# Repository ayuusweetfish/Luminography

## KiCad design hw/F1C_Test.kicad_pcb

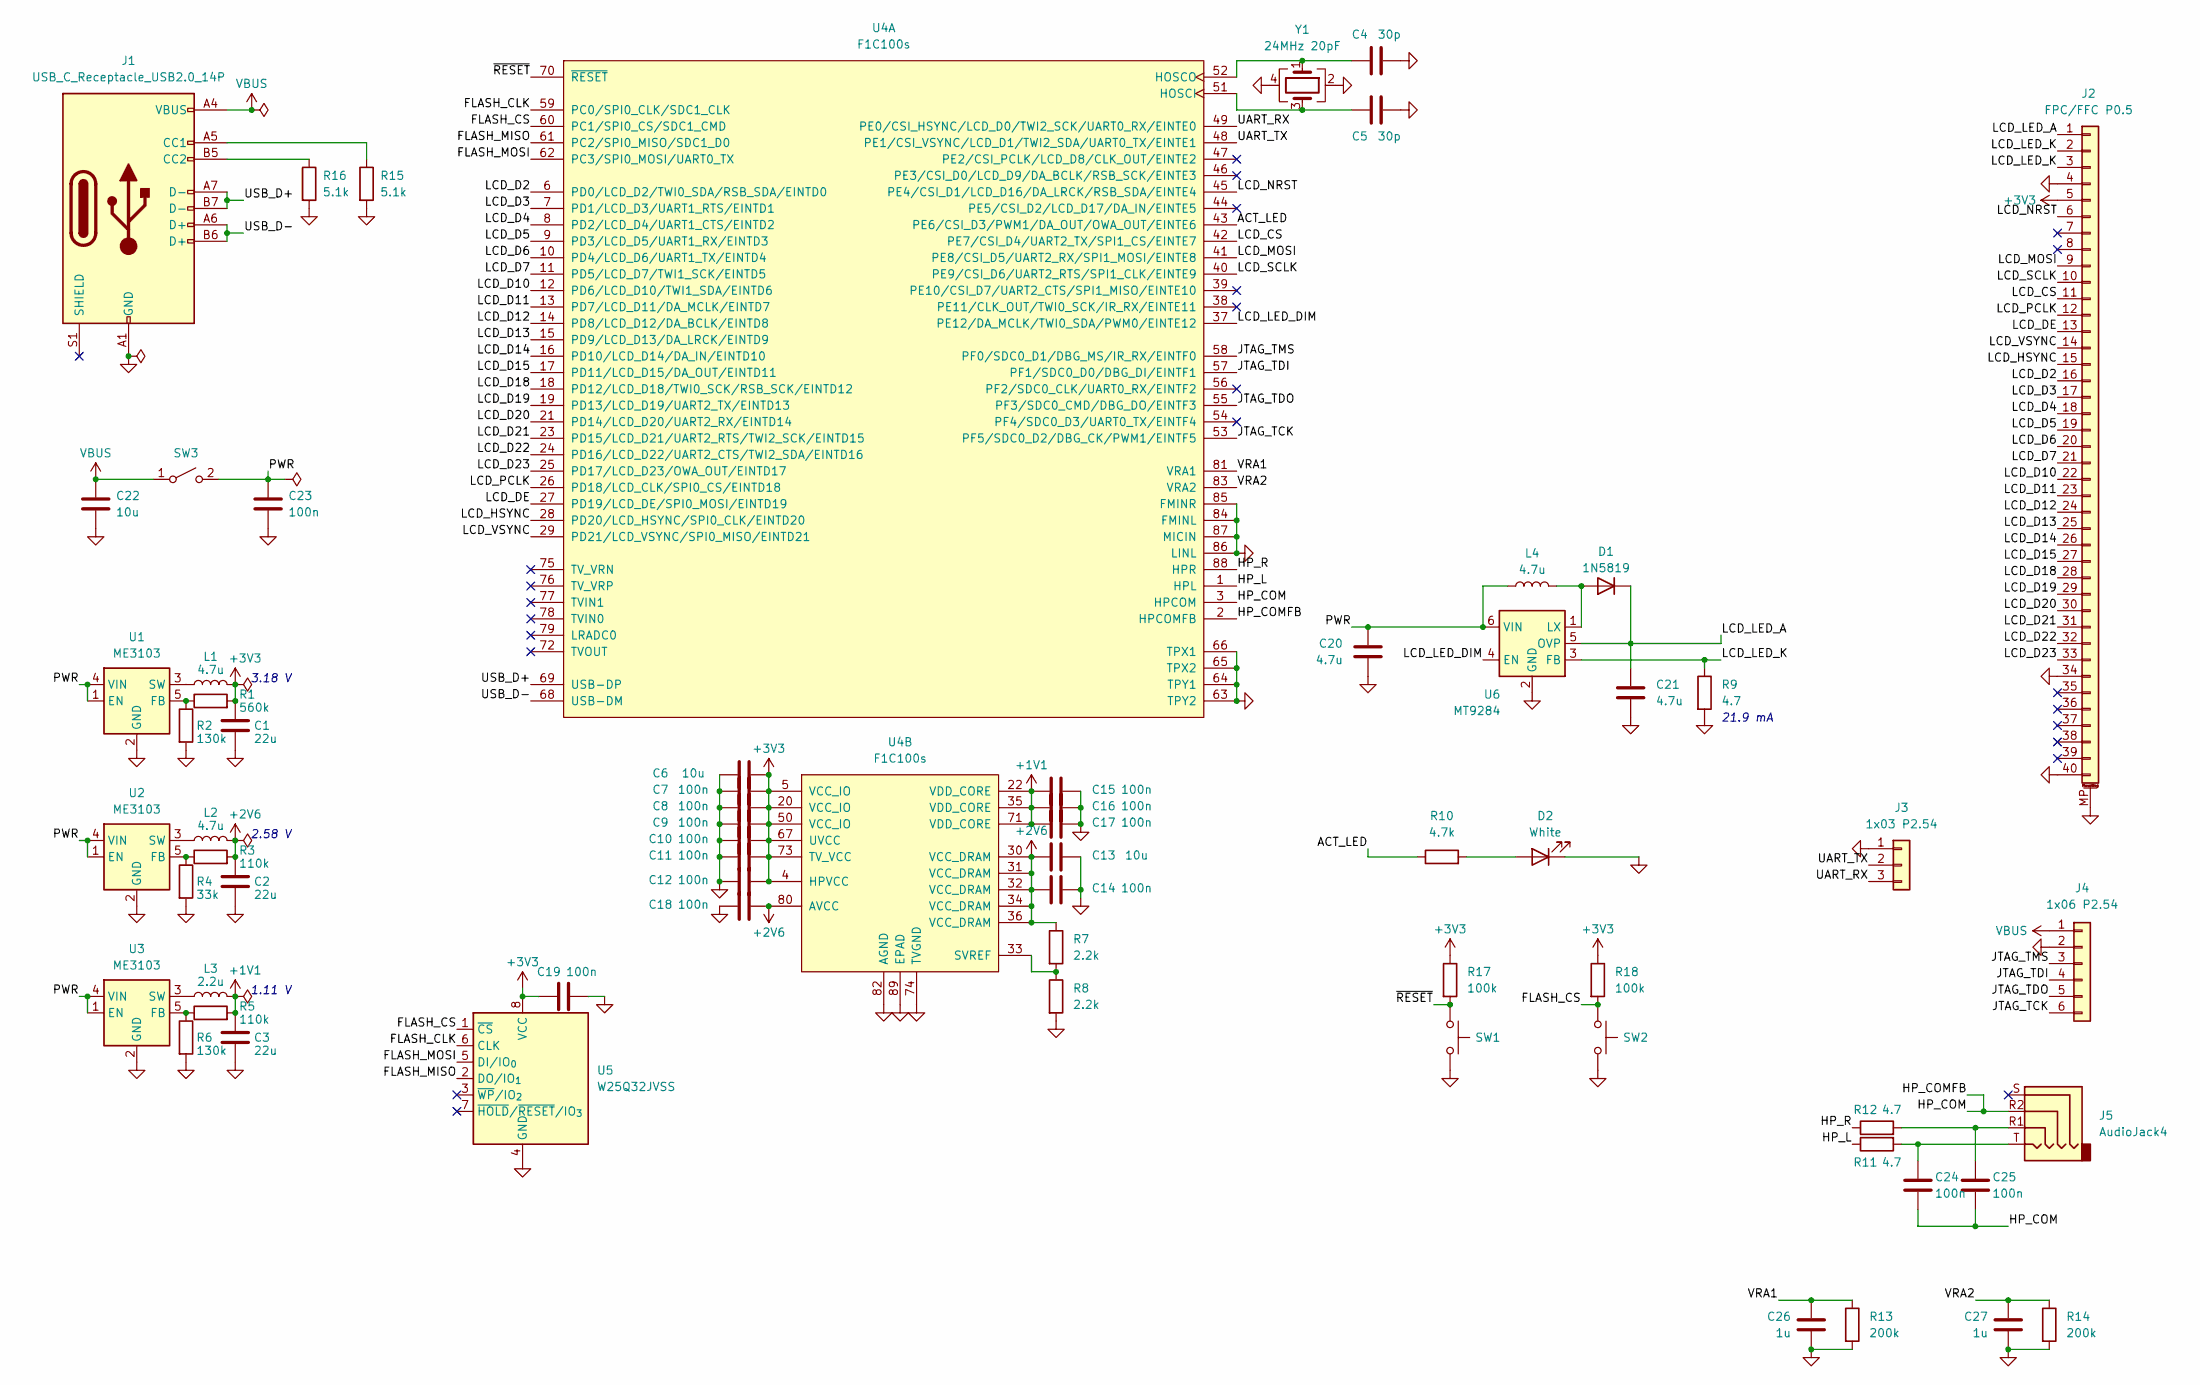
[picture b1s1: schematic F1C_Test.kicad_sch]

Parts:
C1, C2, C3: 22u; C_0603_1608Metric
C4, C5: 30p; C_0402_1005Metric
C6, C13, C22: 10u; C_0402_1005Metric
C7, C8, C9, C10, C11, C12, C14, C15, C16, C17, C18, C19, C23, C24, C25: 100n; C_0402_1005Metric
C20, C21: 4.7u; C_0402_1005Metric
C26, C27: 1u; C_0402_1005Metric
D1: 1N5819; D_SOD-323
D2: White; LED_0603_1608Metric
J1: USB_C_Receptacle_USB2.0_14P; USB_C_Receptacle_HRO_TYPE-C-31-M-12; LCSC PN C165948
J2: FPC/FFC P0.5; FPC_1x40_P0.5_R
J3: 1x03 P2.54; PinHeader_1x03_P2.54mm_Vertical
J4: 1x06 P2.54; PinHeader_1x06_P2.54mm_Vertical
J5: AudioJack4; Jack_3.5mm_KoreanHropartsElec_PJ-320D-4A_Horizontal
L1, L2, L4: 4.7u; L_Sunlord_SWPA3015S
L3: 2.2u; L_Sunlord_SWPA3015S
R1: 560k; R_0402_1005Metric
R2, R6: 130k; R_0402_1005Metric
R3, R5: 110k; R_0402_1005Metric
R4: 33k; R_0402_1005Metric
R7, R8: 2.2k; R_0402_1005Metric
R9, R11, R12: 4.7; R_0402_1005Metric
R10: 4.7k; R_0402_1005Metric
R13, R14: 200k; R_0402_1005Metric
R15, R16: 5.1k; R_0402_1005Metric
R17, R18: 100k; R_0402_1005Metric
SW1, SW2: SW_Push; SW_Push_1TS009xxxx-xxxx-xxxx_6x6x5mm
SW3: SW_SPST; SPST_1x01_P2.54
U1, U2, U3: ME3103; SOT-23-5
U4: F1C100s; QFN40P1000X1000X90-89N-D
U5: W25Q32JVSS; SOIC-8_5.3x5.3mm_P1.27mm
U6: MT9284; SOT-23-6
Y1: 24MHz 20pF; Crystal_SMD_3225-4Pin_3.2x2.5mm; LCSC PN C5339095

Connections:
+1V1: C3.1, C15.2, C16.2, C17.2, L3.2, R5.2, U4.22 (VDD_CORE), U4.35 (VDD_CORE), U4.71 (VDD_CORE)
+2V6: C2.1, C13.2, C14.2, C18.2, L2.2, R3.2, R7.1, U4.30 (VCC_DRAM), U4.31 (VCC_DRAM), U4.32 (VCC_DRAM), U4.34 (VCC_DRAM), U4.36 (VCC_DRAM), U4.80 (AVCC)
+3V3: C1.1, C6.2, C7.2, C8.2, C9.2, C10.2, C11.2, C12.2, C19.1, J2.5, L1.2, R1.2, R17.1, R18.1, U4.4 (HPVCC), U4.5 (VCC_IO), U4.20 (VCC_IO), U4.50 (VCC_IO), U4.67 (UVCC), U4.73 (TV_VCC), U5.8 (VCC)
/ACT_LED: R10.1, U4.43 (PE6/CSI_D3/PWM1/DA_OUT/OWA_OUT/EINTE6)
/FLASH_CLK: U4.59 (PC0/SPI0_CLK/SDC1_CLK), U5.6 (CLK)
/FLASH_CS: R18.2, SW2.1, U4.60 (PC1/SPI0_CS/SDC1_CMD), U5.1 (~CS)
/FLASH_MISO: U4.61 (PC2/SPI0_MISO/SDC1_D0), U5.2 (DO/IO_{1})
/FLASH_MOSI: U4.62 (PC3/SPI0_MOSI/UART0_TX), U5.5 (DI/IO_{0})
/HP_COM: C24.2, C25.2, J5.R2, U4.2 (HPCOMFB), U4.3 (HPCOM)
/HP_L: R11.1, U4.1 (HPL)
/HP_R: R12.1, U4.88 (HPR)
/JTAG_TCK: J4.6, U4.53 (PF5/SDC0_D2/DBG_CK/PWM1/EINTF5)
/JTAG_TDI: J4.4, U4.57 (PF1/SDC0_D0/DBG_DI/EINTF1)
/JTAG_TDO: J4.5, U4.55 (PF3/SDC0_CMD/DBG_DO/EINTF3)
/JTAG_TMS: J4.3, U4.58 (PF0/SDC0_D1/DBG_MS/IR_RX/EINTF0)
/LCD_CS: J2.11, U4.42 (PE7/CSI_D4/UART2_TX/SPI1_CS/EINTE7)
/LCD_D2: J2.16, U4.6 (PD0/LCD_D2/TWI0_SDA/RSB_SDA/EINTD0)
/LCD_D3: J2.17, U4.7 (PD1/LCD_D3/UART1_RTS/EINTD1)
/LCD_D4: J2.18, U4.8 (PD2/LCD_D4/UART1_CTS/EINTD2)
/LCD_D5: J2.19, U4.9 (PD3/LCD_D5/UART1_RX/EINTD3)
/LCD_D6: J2.20, U4.10 (PD4/LCD_D6/UART1_TX/EINTD4)
/LCD_D7: J2.21, U4.11 (PD5/LCD_D7/TWI1_SCK/EINTD5)
/LCD_D10: J2.22, U4.12 (PD6/LCD_D10/TWI1_SDA/EINTD6)
/LCD_D11: J2.23, U4.13 (PD7/LCD_D11/DA_MCLK/EINTD7)
/LCD_D12: J2.24, U4.14 (PD8/LCD_D12/DA_BCLK/EINTD8)
/LCD_D13: J2.25, U4.15 (PD9/LCD_D13/DA_LRCK/EINTD9)
/LCD_D14: J2.26, U4.16 (PD10/LCD_D14/DA_IN/EINTD10)
/LCD_D15: J2.27, U4.17 (PD11/LCD_D15/DA_OUT/EINTD11)
/LCD_D18: J2.28, U4.18 (PD12/LCD_D18/TWI0_SCK/RSB_SCK/EINTD12)
/LCD_D19: J2.29, U4.19 (PD13/LCD_D19/UART2_TX/EINTD13)
/LCD_D20: J2.30, U4.21 (PD14/LCD_D20/UART2_RX/EINTD14)
/LCD_D21: J2.31, U4.23 (PD15/LCD_D21/UART2_RTS/TWI2_SCK/EINTD15)
/LCD_D22: J2.32, U4.24 (PD16/LCD_D22/UART2_CTS/TWI2_SDA/EINTD16)
/LCD_D23: J2.33, U4.25 (PD17/LCD_D23/OWA_OUT/EINTD17)
/LCD_DE: J2.13, U4.27 (PD19/LCD_DE/SPI0_MOSI/EINTD19)
/LCD_HSYNC: J2.15, U4.28 (PD20/LCD_HSYNC/SPI0_CLK/EINTD20)
/LCD_LED_A: C21.1, D1.1 (K), J2.1, U6.5 (OVP)
/LCD_LED_DIM: U4.37 (PE12/DA_MCLK/TWI0_SDA/PWM0/EINTE12), U6.4 (EN)
/LCD_LED_K: J2.2, J2.3, R9.1, U6.3 (FB)
/LCD_MOSI: J2.9, U4.41 (PE8/CSI_D5/UART2_RX/SPI1_MOSI/EINTE8)
/LCD_NRST: J2.6, U4.45 (PE4/CSI_D1/LCD_D16/DA_LRCK/RSB_SDA/EINT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)
/LCD_PCLK: J2.12, U4.26 (PD18/LCD_CLK/SPI0_CS/EINTD18)
/LCD_SCLK: J2.10, U4.40 (PE9/CSI_D6/UART2_RTS/SPI1_CLK/EINTE9)
/LCD_VSYNC: J2.14, U4.29 (PD21/LCD_VSYNC/SPI0_MISO/EINTD21)
/PWR: C20.1, C23.1, L4.1, SW3.2 (B), U1.1 (EN), U1.4 (VIN), U2.1 (EN), U2.4 (VIN), U3.1 (EN), U3.4 (VIN), U6.6 (VIN)
/UART_RX: J3.3, U4.49 (PE0/CSI_HSYNC/LCD_D0/TWI2_SCK/UART0_RX/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)
/UART_TX: J3.2, U4.48 (PE1/CSI_VSYNC/LCD_D1/TWI2_SDA/UART0_TX/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)
/USB_D+: J1.A7 (D-), J1.B7 (D-), U4.69 (USB-DP)
/USB_D-: J1.A6 (D+), J1.B6 (D+), U4.68 (USB-DM)
/VRA1: C26.1, R13.1, U4.81 (VRA1)
/VRA2: C27.1, R14.1, U4.83 (VRA2)
/~RESET: R17.2, SW1.1, U4.70 (~RESET)
GND: C1.2, C2.2, C3.2, C4.2, C5.2, C6.1, C7.1, C8.1, C9.1, C10.1, C11.1, C12.1, C13.1, C14.1, C15.1, C16.1, C17.1, C18.1, C19.2, C20.2, C21.2, C22.2, C23.2, C26.2, C27.2, D2.1 (K), J1.A1 (GND), J1.A12 (GND), J1.B1 (GND), J1.B12 (GND), J2.4, J2.34, J2.40, J2.MP (MountPin), J3.1, J4.2, R2.2, R4.2, R6.2, R8.2, R9.2, R13.2, R14.2, R15.2, R16.2, SW1.2, SW2.2, U1.2 (GND), U2.2 (GND), U3.2 (GND), U4.63 (TPY2), U4.64 (TPY1), U4.65 (TPX2), U4.66 (TPX1), U4.74 (TVGND), U4.82 (AGND), U4.84 (FMINL), U4.85 (FMINR), U4.86 (LINL), U4.87 (MICIN), U4.89 (EPAD), U5.4 (GND), U6.2 (GND), Y1.2, Y1.4
unnamed: C24.1, J5.T, R11.2
unnamed: C25.1, J5.R1, R12.2
unnamed: D1.2 (A), L4.2, U6.1 (LX)
unnamed: D2.2 (A), R10.2
unnamed: J1.A5 (CC1), R15.1
unnamed: J1.B5 (CC2), R16.1
unnamed: R1.1, R2.1, U1.5 (FB)
unnamed: L1.1, U1.3 (SW)
unnamed: R3.1, R4.1, U2.5 (FB)
unnamed: L2.1, U2.3 (SW)
unnamed: R5.1, R6.1, U3.5 (FB)
unnamed: L3.1, U3.3 (SW)
unnamed: C5.1, U4.51 (HOSCI), Y1.3
unnamed: C4.1, U4.52 (HOSCO), Y1.1
unnamed: R7.2, R8.1, U4.33 (SVREF)
VBUS: C22.1, J1.A4 (VBUS), J1.A9 (VBUS), J1.B4 (VBUS), J1.B9 (VBUS), J4.1, SW3.1 (A)

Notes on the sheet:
21.9 mA
1.11 V
3.18 V
2.58 V

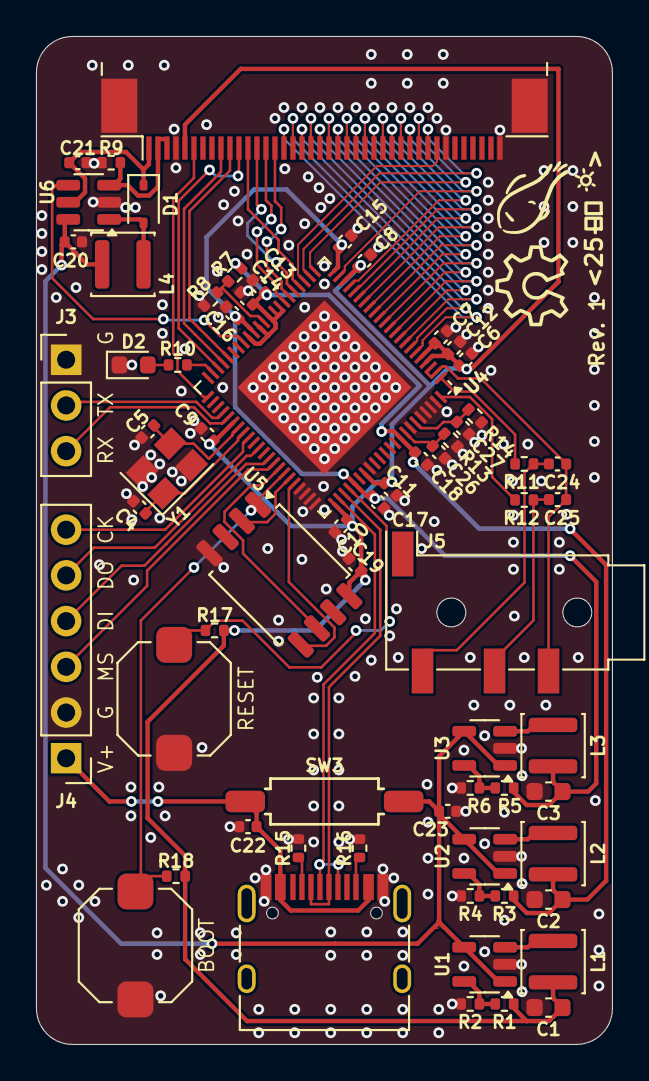
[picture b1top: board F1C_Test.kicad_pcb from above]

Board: 2 copper layers, 32.0 x 56.0 mm, 66 parts (0 on the bottom side), 69 nets.

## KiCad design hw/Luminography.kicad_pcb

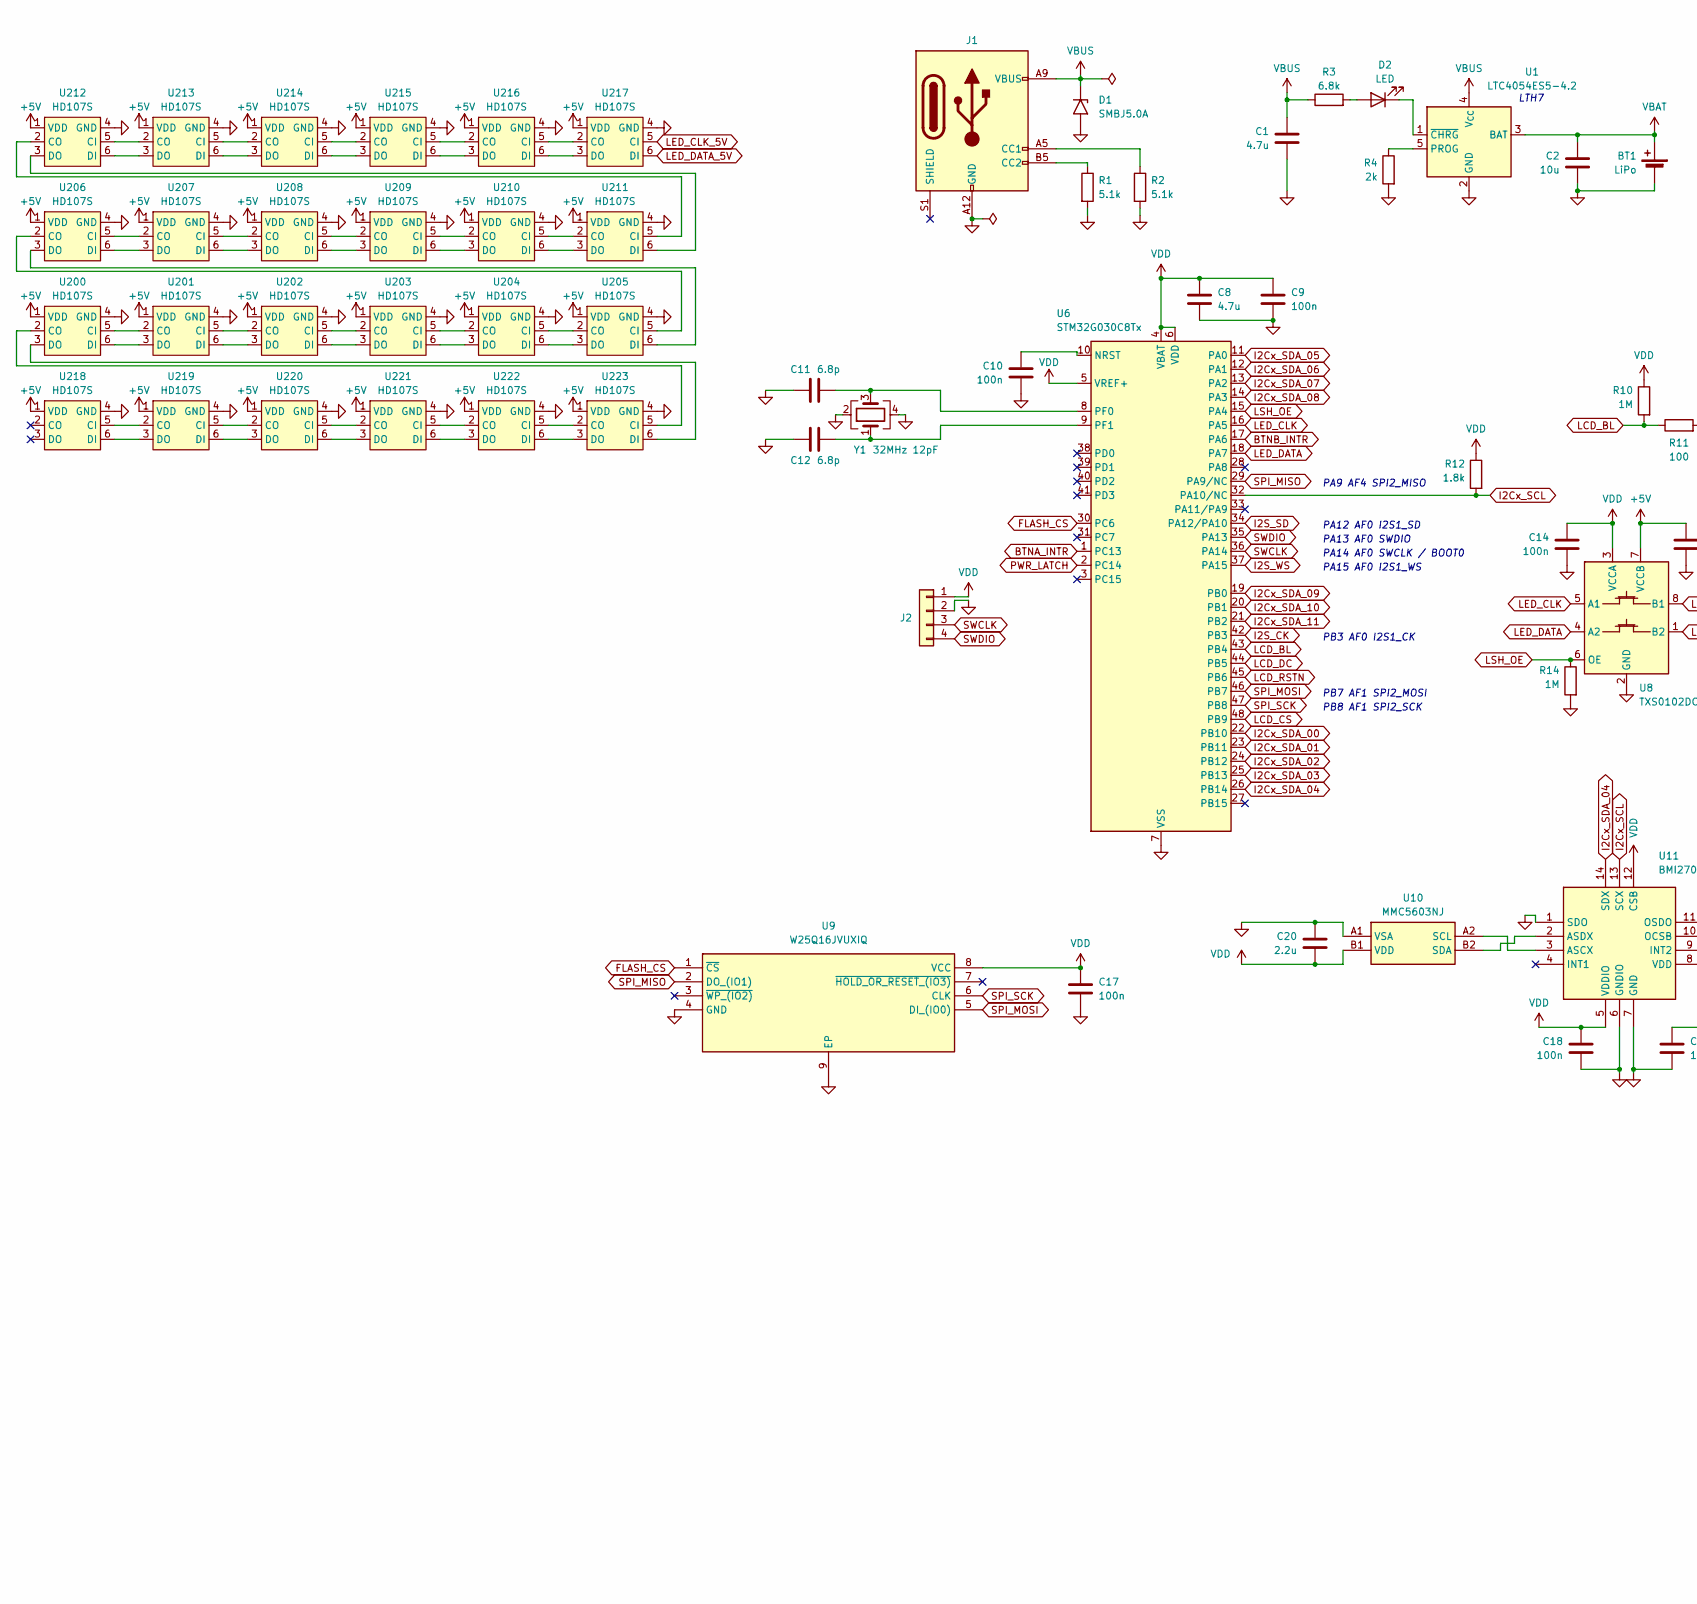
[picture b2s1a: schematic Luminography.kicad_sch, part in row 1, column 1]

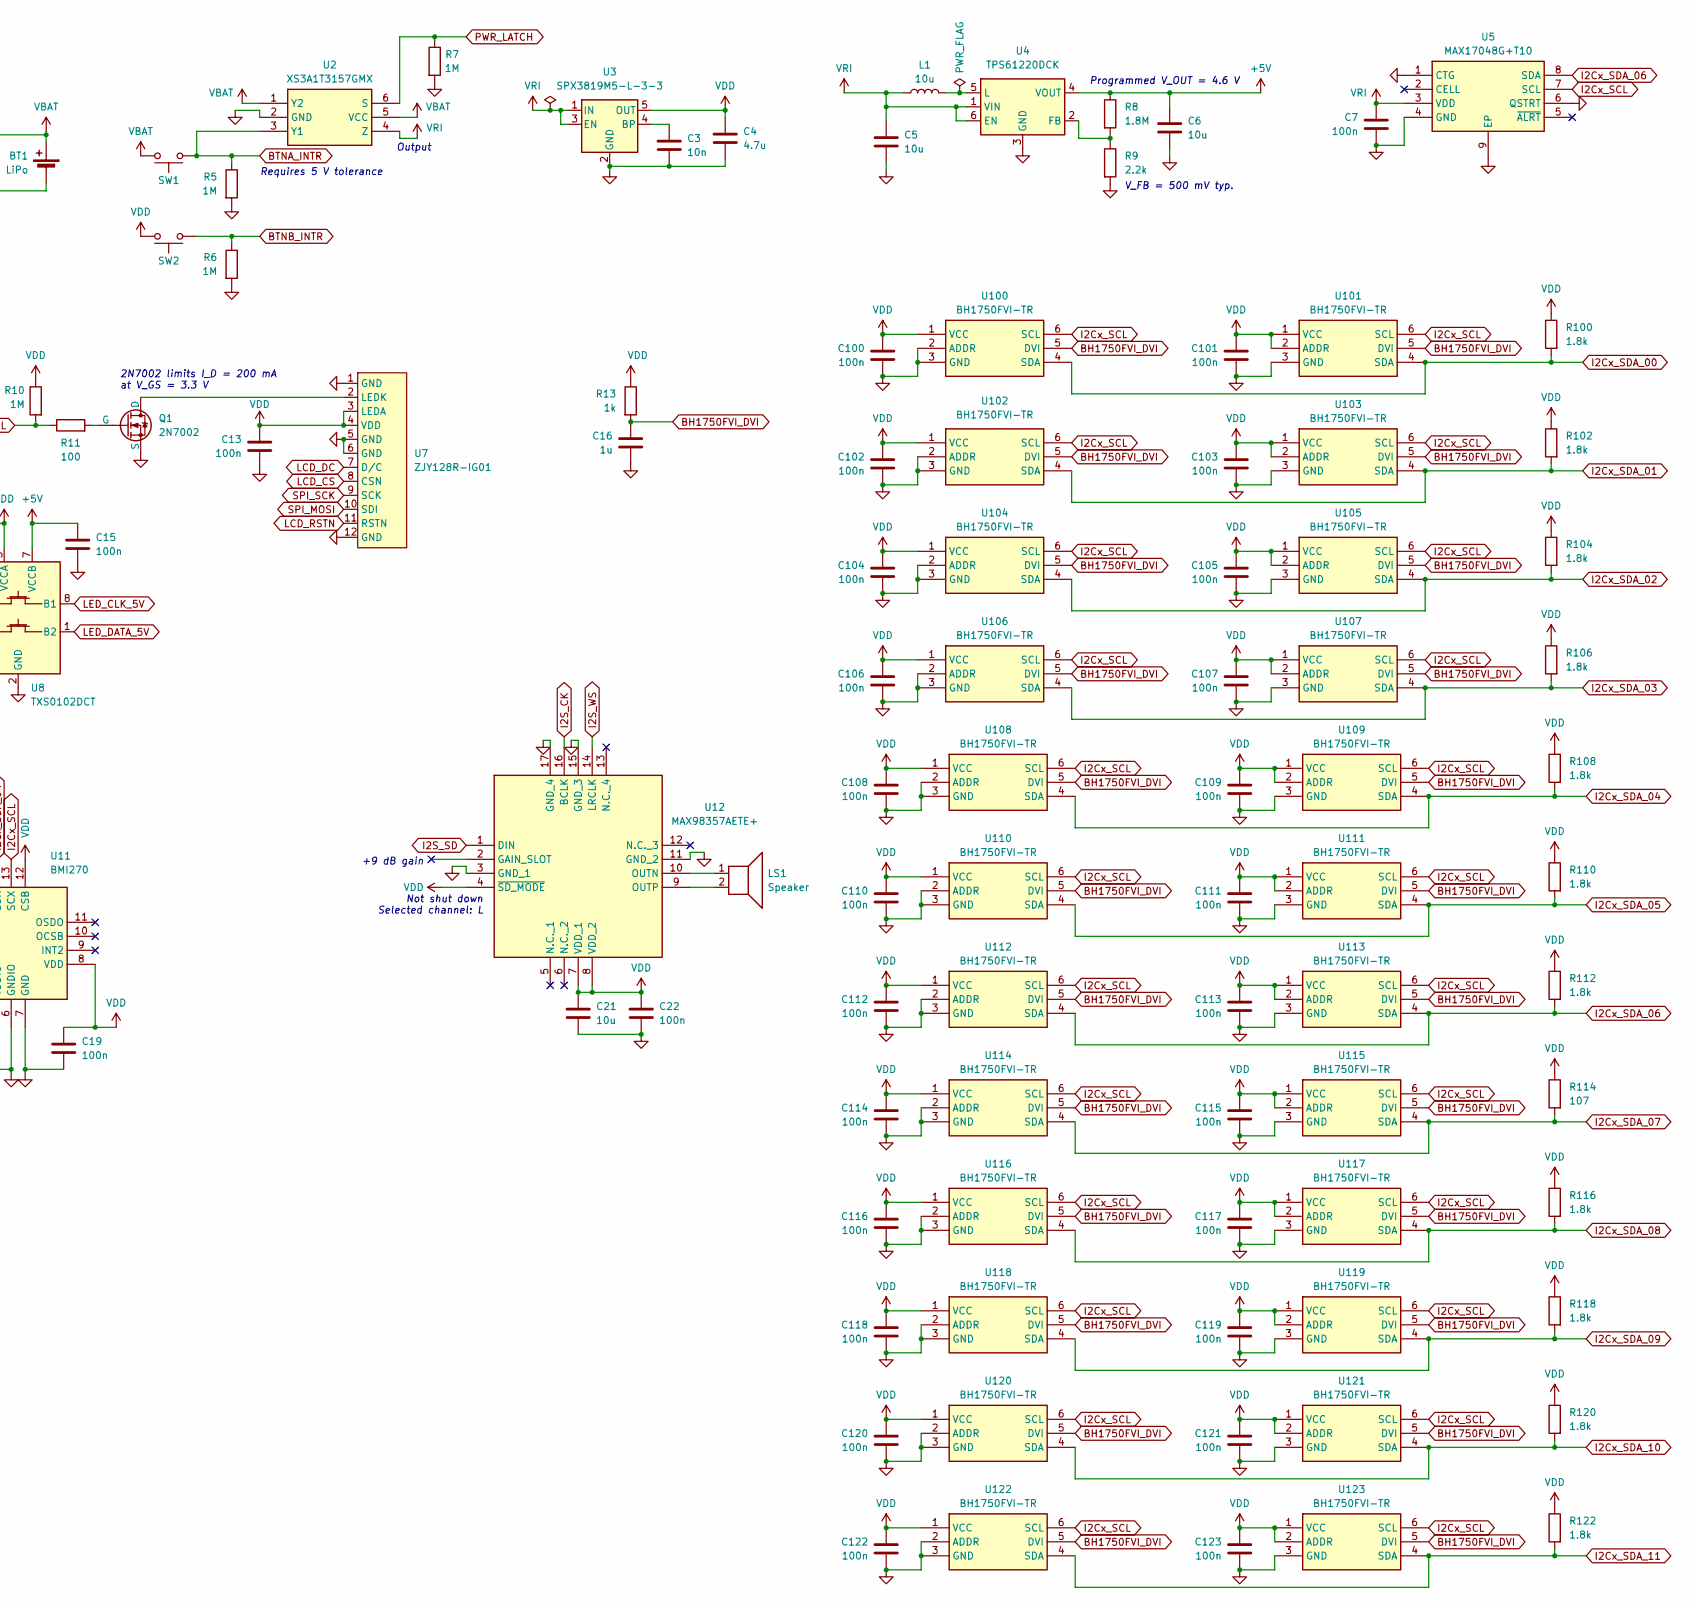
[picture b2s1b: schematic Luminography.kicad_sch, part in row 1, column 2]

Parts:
BT1: LiPo; Pads_1x02_P2.5
C1, C4, C8: 4.7u; C_0402_1005Metric
C2, C5, C6, C21: 10u; C_0402_1005Metric
C3: 10n; C_0402_1005Metric
C7, C9, C10, C13, C14, C15, C17, C18, C19, C22, C100, C101, C102, C103, C104, C105, C106, C107, C108, C109, C110, C111, C112, C113, C114, C115, C116, C117, C118, C119, C120, C121, C122, C123: 100n; C_0402_1005Metric
C11, C12: 6.8p; C_0402_1005Metric
C16: 1u; C_0402_1005Metric
C20: 2.2u; C_0402_1005Metric
D1: SMBJ5.0A; D_SMB
D2: LED; LED_0603_1608Metric
J1: USB_C_Receptacle_PowerOnly_6P; USB_C_Receptacle
J2: Conn_01x04; TestPoints_1x04_P2.0
L1: 10u; L_Sunlord_SWPA252012S
LS1: Speaker; Pads_1x02_P2.5
Q1: 2N7002; SOT-23
R1, R2: 5.1k; R_0402_1005Metric
R3: 6.8k; R_0402_1005Metric
R4: 2k; R_0402_1005Metric
R5, R6, R7, R10, R14: 1M; R_0402_1005Metric
R8: 1.8M; R_0402_1005Metric
R9: 2.2k; R_0402_1005Metric
R11: 100; R_0402_1005Metric
R12, R100, R102, R104, R106, R108, R110, R112, R116, R118, R120, R122: 1.8k; R_0402_1005Metric
R13: 1k; R_0402_1005Metric
R114: 107; R_0402_1005Metric
SW1, SW2: SW_Push; SW_SPST_TL3342
U1: LTC4054ES5-4.2; TSOT-23-5
U2: XS3A1T3157GMX; Manufacturer_Part_Number XS3A1T3157GMX; Mouser Part Number 771-XS3A1T3157GMX
U3: SPX3819M5-L-3-3; SOT-23-5
U4: TPS61220DCK; Texas_R-PDSO-G6
U5: MAX17048G+T10; SON50P200X200X80-9N-D; Manufacturer_Part_Number MAX17048G+T10; Mouser Part Number 700-MAX17048G+T10
U6: STM32G030C8Tx; LQFP-48_7x7mm_P0.5mm
U7: ZJY128R-IG01; FPC_12_P0.7
U8: TXS0102DCT; SSOP-8_2.95x2.8mm_P0.65mm
U9: W25Q16JVUXIQ; SON50P300X200X60-9N; Manufacturer_Part_Number W25Q16JVUXIQ
U10: MMC5603NJ; Manufacturer_Part_Number MMC5603NJ; Mouser Part Number 438-MMC5603NJ
U11: BMI270; QFN50P300X250X87-14N; Manufacturer_Part_Number BMI270; Mouser Part Number 262-BMI270
U12: MAX98357AETE+; QFN50P300X300X80-17N; Manufacturer_Part_Number MAX98357AETE+; Mouser Part Number 700-MAX98357AETE+
U100, U101, U102, U103, U104, U105, U106, U107, U108, U109, U110, U111, U112, U113, U114, U115, U116, U117, U118, U119, U120, U121, U122, U123: BH1750FVI-TR; WSOF6; Manufacturer_Part_Number BH1750FVI-TR; Mouser Part Number 755-BH1750FVI-TR
U200, U201, U202, U203, U204, U205, U206, U207, U208, U209, U210, U211, U212, U213, U214, U215, U216, U217, U218, U219, U220, U221, U222, U223: HD107S; HD107S_2020_6
Y1: 32MHz 12pF; Crystal_SMD_3225-4Pin_3.2x2.5mm

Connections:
+5V: C6.1, C15.1, R8.1, U4.4 (VOUT), U8.7 (VCCB), U200.1 (VDD), U201.1 (VDD), U202.1 (VDD), U203.1 (VDD), U204.1 (VDD), U205.1 (VDD), U206.1 (VDD), U207.1 (VDD), U208.1 (VDD), U209.1 (VDD), U210.1 (VDD), U211.1 (VDD), U212.1 (VDD), U213.1 (VDD), U214.1 (VDD), U215.1 (VDD), U216.1 (VDD), U217.1 (VDD), U218.1 (VDD), U219.1 (VDD), U220.1 (VDD), U221.1 (VDD), U222.1 (VDD), U223.1 (VDD)
BH1750FVI_DVI: C16.1, R13.2, U100.5 (DVI), U101.5 (DVI), U102.5 (DVI), U103.5 (DVI), U104.5 (DVI), U105.5 (DVI), U106.5 (DVI), U107.5 (DVI), U108.5 (DVI), U109.5 (DVI), U110.5 (DVI), U111.5 (DVI), U112.5 (DVI), U113.5 (DVI), U114.5 (DVI), U115.5 (DVI), U116.5 (DVI), U117.5 (DVI), U118.5 (DVI), U119.5 (DVI), U120.5 (DVI), U121.5 (DVI), U122.5 (DVI), U123.5 (DVI)
BTNA_INTR: R5.1, SW1.2, U2.3 (Y1), U6.1 (PC13)
BTNB_INTR: R6.1, SW2.2, U6.17 (PA6)
FLASH_CS: U6.30 (PC6), U9.1 (~CS)
GND: BT1.2 (-), C1.2, C2.2, C3.2, C4.2, C5.2, C6.2, C7.2, C8.2, C9.2, C10.2, C11.1, C12.1, C13.2, C14.2, C15.2, C16.2, C17.1, C18.2, C19.2, C20.1, C21.2, C22.2, C100.2, C101.2, C102.2, C103.2, C104.2, C105.2, C106.2, C107.2, C108.2, C109.2, C110.2, C111.2, C112.2, C113.2, C114.2, C115.2, C116.2, C117.2, C118.2, C119.2, C120.2, C121.2, C122.2, C123.2, D1.2 (A2), J1.A12 (GND), J1.B12 (GND), J2.2, Q1.2 (S), R1.2, R2.2, R4.2, R5.2, R6.2, R7.2, R9.2, R14.2, U1.2 (GND), U2.2 (GND), U3.2 (GND), U4.3 (GND), U5.1 (CTG), U5.4 (GND), U5.6 (QSTRT), U5.9 (EP), U6.7 (VSS), U7.1 (GND), U7.5 (GND), U7.6 (GND), U7.12 (GND), U8.2 (GND), U9.4 (GND), U9.9 (EP), U10.A1 (VSA), U11.1 (SDO), U11.6 (GNDIO), U11.7 (GND), U12.3 (GND_1), U12.11 (GND_2), U12.15 (GND_3), U12.17 (GND_4), U100.2 (ADDR), U100.3 (GND), U101.3 (GND), U102.2 (ADDR), U102.3 (GND), U103.3 (GND), U104.2 (ADDR), U104.3 (GND), U105.3 (GND), U106.2 (ADDR), U106.3 (GND), U107.3 (GND), U108.2 (ADDR), U108.3 (GND), U109.3 (GND), U110.2 (ADDR), U110.3 (GND), U111.3 (GND), U112.2 (ADDR), U112.3 (GND), U113.3 (GND), U114.2 (ADDR), U114.3 (GND), U115.3 (GND), U116.2 (ADDR), U116.3 (GND), U117.3 (GND), U118.2 (ADDR), U118.3 (GND), U119.3 (GND), U120.2 (ADDR), U120.3 (GND), U121.3 (GND), U122.2 (ADDR), U122.3 (GND), U123.3 (GND), U200.4 (GND), U201.4 (GND), U202.4 (GND), U203.4 (GND), U204.4 (GND), U205.4 (GND), U206.4 (GND), U207.4 (GND), U208.4 (GND), U209.4 (GND), U210.4 (GND), U211.4 (GND), U212.4 (GND), U213.4 (GND), U214.4 (GND), U215.4 (GND), U216.4 (GND), U217.4 (GND), U218.4 (GND), U219.4 (GND), U220.4 (GND), U221.4 (GND), U222.4 (GND), U223.4 (GND), Y1.2, Y1.4
I2Cx_SCL: R12.2, U5.7 (SCL), U6.32 (PA10/NC), U11.13 (SCX), U100.6 (SCL), U101.6 (SCL), U102.6 (SCL), U103.6 (SCL), U104.6 (SCL), U105.6 (SCL), U106.6 (SCL), U107.6 (SCL), U108.6 (SCL), U109.6 (SCL), U110.6 (SCL), U111.6 (SCL), U112.6 (SCL), U113.6 (SCL), U114.6 (SCL), U115.6 (SCL), U116.6 (SCL), U117.6 (SCL), U118.6 (SCL), U119.6 (SCL), U120.6 (SCL), U121.6 (SCL), U122.6 (SCL), U123.6 (SCL)
I2Cx_SDA_00: R100.2, U6.22 (PB10), U100.4 (SDA), U101.4 (SDA)
I2Cx_SDA_01: R102.2, U6.23 (PB11), U102.4 (SDA), U103.4 (SDA)
I2Cx_SDA_02: R104.2, U6.24 (PB12), U104.4 (SDA), U105.4 (SDA)
I2Cx_SDA_03: R106.2, U6.25 (PB13), U106.4 (SDA), U107.4 (SDA)
I2Cx_SDA_04: R108.2, U6.26 (PB14), U11.14 (SDX), U108.4 (SDA), U109.4 (SDA)
I2Cx_SDA_05: R110.2, U6.11 (PA0), U110.4 (SDA), U111.4 (SDA)
I2Cx_SDA_06: R112.2, U5.8 (SDA), U6.12 (PA1), U112.4 (SDA), U113.4 (SDA)
I2Cx_SDA_07: R114.2, U6.13 (PA2), U114.4 (SDA), U115.4 (SDA)
I2Cx_SDA_08: R116.2, U6.14 (PA3), U116.4 (SDA), U117.4 (SDA)
I2Cx_SDA_09: R118.2, U6.19 (PB0), U118.4 (SDA), U119.4 (SDA)
I2Cx_SDA_10: R120.2, U6.20 (PB1), U120.4 (SDA), U121.4 (SDA)
I2Cx_SDA_11: R122.2, U6.21 (PB2), U122.4 (SDA), U123.4 (SDA)
I2S_CK: U6.42 (PB3), U12.16 (BCLK)
I2S_SD: U6.34 (PA12/PA10), U12.1 (DIN)
I2S_WS: U6.37 (PA15), U12.14 (LRCLK)
LCD_BL: R10.2, R11.1, U6.43 (PB4)
LCD_CS: U6.48 (PB9), U7.8 (CSN)
LCD_DC: U6.44 (PB5), U7.7 (D/C)
LCD_RSTN: U6.45 (PB6), U7.11 (RSTN)
LED_CLK: U6.16 (PA5), U8.5 (A1)
LED_CLK_5V: U8.8 (B1), U217.5 (CI)
LED_DATA: U6.18 (PA7), U8.4 (A2)
LED_DATA_5V: U8.1 (B2), U217.6 (DI)
LSH_OE: R14.1, U6.15 (PA4), U8.6 (OE)
unnamed: D2.2 (A), R3.2
unnamed: D2.1 (K), U1.1 (~CHRG)
unnamed: J1.A5 (CC1), R2.1
unnamed: J1.B5 (CC2), R1.1
unnamed: Q1.3 (D), U7.2 (LEDK)
unnamed: Q1.1 (G), R11.2
unnamed: R4.1, U1.5 (PROG)
unnamed: C3.1, U3.4 (BP)
unnamed: R8.2, R9.1, U4.2 (FB)
unnamed: L1.2, U4.5 (L)
unnamed: C10.1, U6.10 (NRST)
unnamed: C11.2, U6.8 (PF0), Y1.3
unnamed: C12.2, U6.9 (PF1), Y1.1
unnamed: U10.A2 (SCL), U11.3 (ASCX)
unnamed: U10.B2 (SDA), U11.2 (ASDX)
unnamed: LS1.1, U12.10 (OUTN)
unnamed: LS1.2, U12.9 (OUTP)
unnamed: U200.5 (CI), U201.2 (CO)
unnamed: U200.2 (CO), U223.5 (CI)
unnamed: U200.6 (DI), U201.3 (DO)
unnamed: U200.3 (DO), U223.6 (DI)
unnamed: U201.5 (CI), U202.2 (CO)
unnamed: U201.6 (DI), U202.3 (DO)
unnamed: U202.5 (CI), U203.2 (CO)
unnamed: U202.6 (DI), U203.3 (DO)
unnamed: U203.5 (CI), U204.2 (CO)
unnamed: U203.6 (DI), U204.3 (DO)
unnamed: U204.5 (CI), U205.2 (CO)
unnamed: U204.6 (DI), U205.3 (DO)
unnamed: U205.5 (CI), U206.2 (CO)
unnamed: U205.6 (DI), U206.3 (DO)
unnamed: U206.5 (CI), U207.2 (CO)
unnamed: U206.6 (DI), U207.3 (DO)
unnamed: U207.5 (CI), U208.2 (CO)
unnamed: U207.6 (DI), U208.3 (DO)
unnamed: U208.5 (CI), U209.2 (CO)
unnamed: U208.6 (DI), U209.3 (DO)
unnamed: U209.5 (CI), U210.2 (CO)
unnamed: U209.6 (DI), U210.3 (DO)
unnamed: U210.5 (CI), U211.2 (CO)
unnamed: U210.6 (DI), U211.3 (DO)
unnamed: U211.5 (CI), U212.2 (CO)
unnamed: U211.6 (DI), U212.3 (DO)
unnamed: U212.5 (CI), U213.2 (CO)
unnamed: U212.6 (DI), U213.3 (DO)
unnamed: U213.5 (CI), U214.2 (CO)
unnamed: U213.6 (DI), U214.3 (DO)
unnamed: U214.5 (CI), U215.2 (CO)
unnamed: U214.6 (DI), U215.3 (DO)
unnamed: U215.5 (CI), U216.2 (CO)
unnamed: U215.6 (DI), U216.3 (DO)
unnamed: U216.5 (CI), U217.2 (CO)
unnamed: U216.6 (DI), U217.3 (DO)
unnamed: U218.5 (CI), U219.2 (CO)
unnamed: U218.6 (DI), U219.3 (DO)
unnamed: U219.5 (CI), U220.2 (CO)
unnamed: U219.6 (DI), U220.3 (DO)
unnamed: U220.5 (CI), U221.2 (CO)
unnamed: U220.6 (DI), U221.3 (DO)
unnamed: U221.5 (CI), U222.2 (CO)
unnamed: U221.6 (DI), U222.3 (DO)
unnamed: U222.5 (CI), U223.2 (CO)
unnamed: U222.6 (DI), U223.3 (DO)
PWR_LATCH: R7.1, U2.6 (S), U6.2 (PC14)
SPI_MISO: U6.29 (PA9/NC), U9.2 (DO_(IO1))
SPI_MOSI: U6.46 (PB7), U7.10 (SDI), U9.5 (DI_(IO0))
SPI_SCK: U6.47 (PB8), U7.9 (SCK), U9.6 (CLK)
SWCLK: J2.3, U6.36 (PA14)
SWDIO: J2.4, U6.35 (PA13)
VBAT: BT1.1 (+), C2.1, SW1.1, U1.3 (BAT), U2.1 (Y2), U2.5 (VCC)
VBUS: C1.1, D1.1 (A1), J1.A9 (VBUS), J1.B9 (VBUS), R3.1, U1.4 (V_{CC})
VDD: C4.1, C8.1, C9.1, C13.1, C14.1, C17.2, C18.1, C19.1, C20.2, C21.1, C22.1, C100.1, C101.1, C102.1, C103.1, C104.1, C105.1, C106.1, C107.1, C108.1, C109.1, C110.1, C111.1, C112.1, C113.1, C114.1, C115.1, C116.1, C117.1, C118.1, C119.1, C120.1, C121.1, C122.1, C123.1, J2.1, R10.1, R12.1, R13.1, R100.1, R102.1, R104.1, R106.1, R108.1, R110.1, R112.1, R114.1, R116.1, R118.1, R120.1, R122.1, SW2.1, U3.5 (OUT), U6.4 (VBAT), U6.5 (VREF+), U6.6 (VDD), U7.3 (LEDA), U7.4 (VDD), U8.3 (VCCA), U9.8 (VCC), U10.B1 (VDD), U11.5 (VDDIO), U11.8 (VDD), U11.12 (CSB), U12.4 (~SD_MODE), U12.7 (VDD_1), U12.8 (VDD_2), U100.1 (VCC), U101.1 (VCC), U101.2 (ADDR), U102.1 (VCC), U103.1 (VCC), U103.2 (ADDR), U104.1 (VCC), U105.1 (VCC), U105.2 (ADDR), U106.1 (VCC), U107.1 (VCC), U107.2 (ADDR), U108.1 (VCC), U109.1 (VCC), U109.2 (ADDR), U110.1 (VCC), U111.1 (VCC), U111.2 (ADDR), U112.1 (VCC), U113.1 (VCC), U113.2 (ADDR), U114.1 (VCC), U115.1 (VCC), U115.2 (ADDR), U116.1 (VCC), U117.1 (VCC), U117.2 (ADDR), U118.1 (VCC), U119.1 (VCC), U119.2 (ADDR), U120.1 (VCC), U121.1 (VCC), U121.2 (ADDR), U122.1 (VCC), U123.1 (VCC), U123.2 (ADDR)
VRI: C5.1, C7.1, L1.1, U2.4 (Z), U3.1 (IN), U3.3 (EN), U4.1 (VIN), U4.6 (EN), U5.3 (VDD)

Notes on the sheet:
Output
+9 dB gain
2N7002 limits I_D = 200 mA at V_GS = 3.3 V
PB8 AF1 SPI2_SCK
PB7 AF1 SPI2_MOSI
PA14 AF0 SWCLK / BOOT0
Not shut down Selected channel: L
PA15 AF0 I2S1_WS
Programmed V_OUT = 4.6 V
Requires 5 V tolerance
PA12 AF0 I2S1_SD
PA13 AF0 SWDIO
LTH7
PA9 AF4 SPI2_MISO
V_FB = 500 mV typ.
PB3 AF0 I2S1_CK

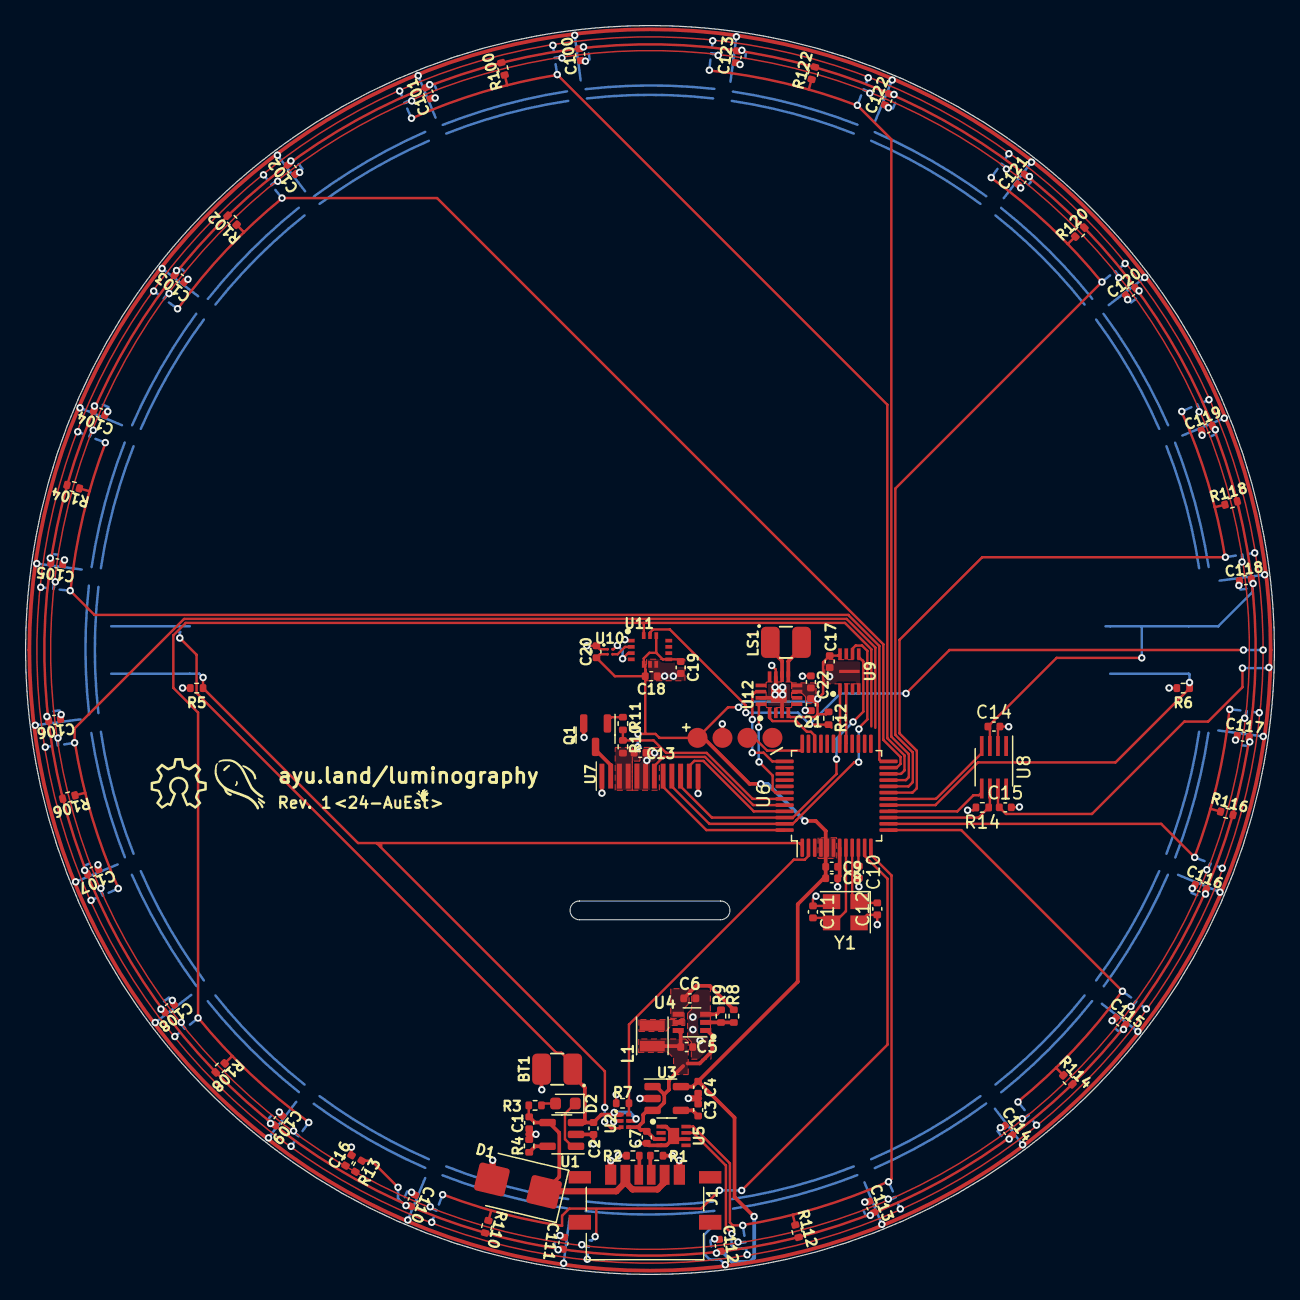
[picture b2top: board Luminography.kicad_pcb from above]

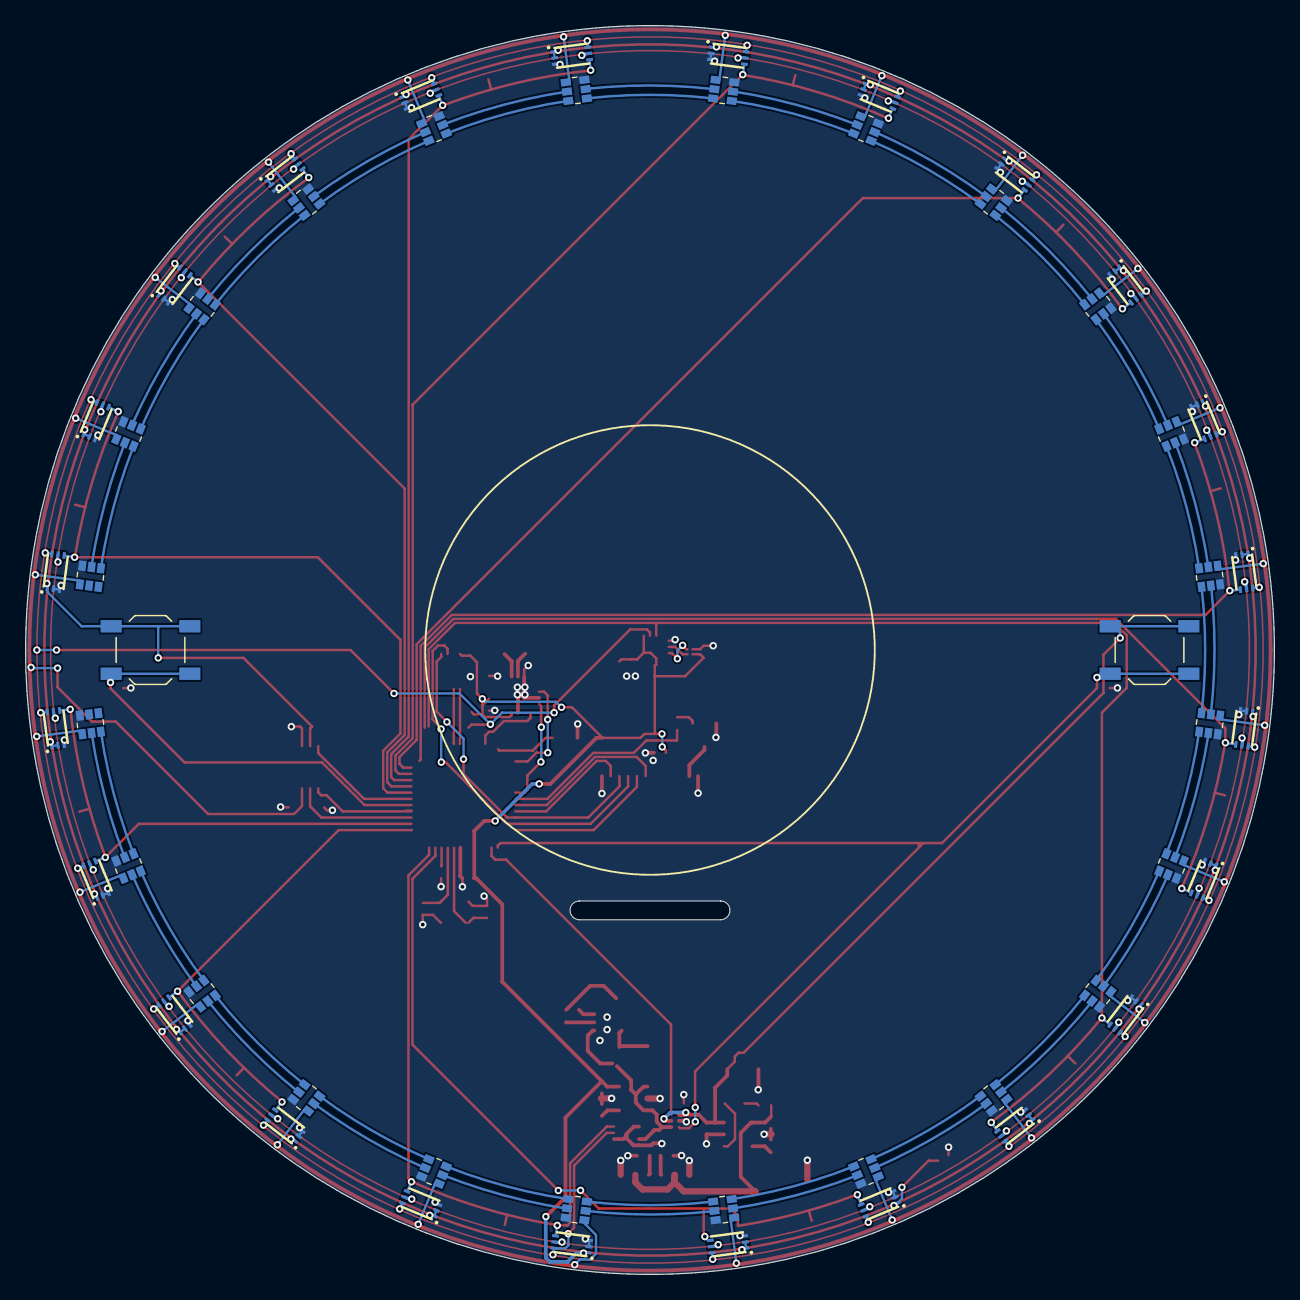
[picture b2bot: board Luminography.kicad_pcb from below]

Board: 2 copper layers, 100.0 x 100.0 mm, 143 parts (50 on the bottom side), 104 nets.

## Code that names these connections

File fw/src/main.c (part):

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  __HAL_RCC_GPIOC_CLK_ENABLE();
  GPIO_InitTypeDef gpio_init;

  // SWD (PA13, PA14)
  gpio_init.Pin = GPIO_PIN_13 | GPIO_PIN_14;
  gpio_init.Mode = GPIO_MODE_AF_PP; // Pass over control to AF peripheral
  gpio_init.Alternate = GPIO_AF0_SWJ;
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  // Start timer early for extra bits of unpredictability
  entropy_clocks_start();

  // LSH_OE (PA4), LED_CLK (PA7), LED_DATA (PA5)
  HAL_GPIO_Init(GPIOA, &(GPIO_InitTypeDef){
    .Pin = GPIO_PIN_4 | GPIO_PIN_5 | GPIO_PIN_7,
    .Mode = GPIO_MODE_OUTPUT_PP,
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  entropy_clocks_stop();
  xoshiro128starstar_next(entropy_pool);

  // LCD_RSTN (PB6), LCD_BL (PB4), LCD_DC (PB5), LCD_CS (PB9)
  HAL_GPIO_Init(GPIOB, &(GPIO_InitTypeDef){
    .Pin = GPIO_PIN_6 | GPIO_PIN_4 | GPIO_PIN_5 | GPIO_PIN_9,
    .Mode = GPIO_MODE_OUTPUT_PP,
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  HAL_NVIC_EnableIRQ(SPI2_IRQn);

  // ======== SPI ========
  // SPI2_MOSI (PB7), SPI2_SCK (PB8)
  HAL_GPIO_Init(GPIOB, &(GPIO_InitTypeDef){
    .Pin = GPIO_PIN_7 | GPIO_PIN_8,
    .Mode = GPIO_MODE_AF_PP,
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
    if (HAL_GPIO_ReadPin(GPIOC, GPIO_PIN_13) == 1 || HAL_GPIO_ReadPin(GPIOA, GPIO_PIN_6) == 1) {
      led_flush();
      HAL_GPIO_WritePin(GPIOC, GPIO_PIN_14, 0); // PWR_LATCH
    }
  }
}
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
